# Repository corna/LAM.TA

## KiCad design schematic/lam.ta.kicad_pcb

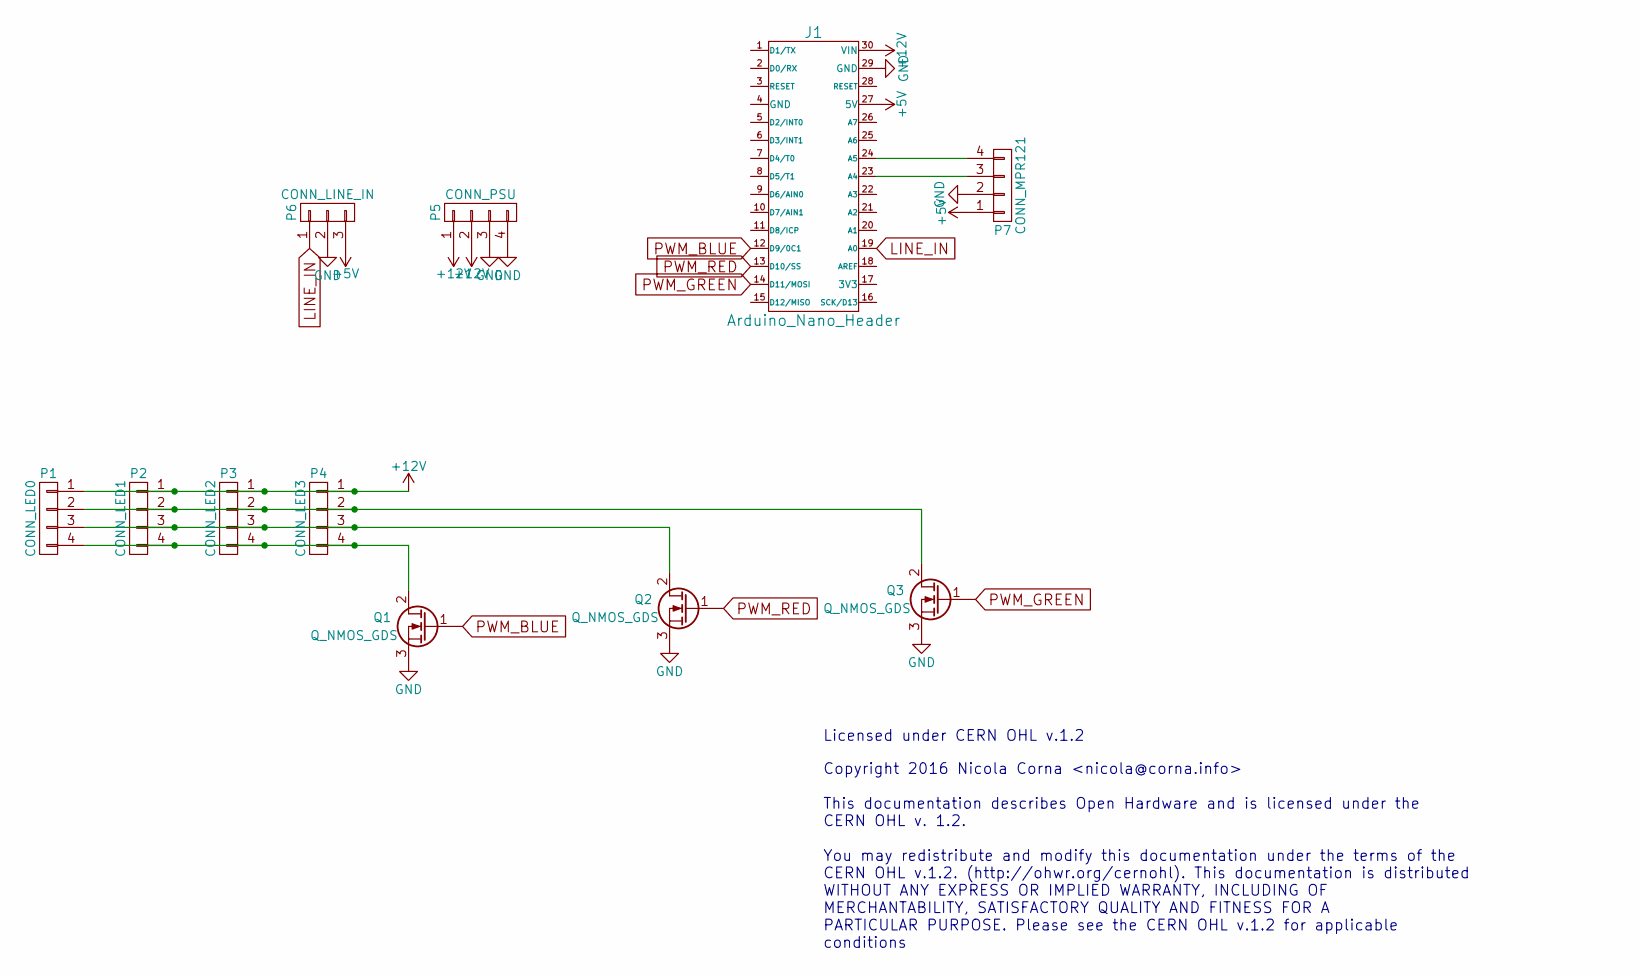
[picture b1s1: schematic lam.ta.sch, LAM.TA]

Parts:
J1: Arduino_Nano_Header; arduino_nano_header
P1: CONN_LED0; Pin_Header_Straight_1x04
P2: CONN_LED1; Pin_Header_Straight_1x04
P3: CONN_LED2; Pin_Header_Straight_1x04
P4: CONN_LED3; Pin_Header_Straight_1x04
P5: CONN_PSU; Pin_Header_Straight_1x04
P6: CONN_LINE_IN; Pin_Header_Straight_1x03
P7: CONN_MPR121; Pin_Header_Straight_1x04
Q1, Q2, Q3: Q_NMOS_GDS; SOT-404

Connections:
+5V: J1.27 (5V), P6.3, P7.1
+12V: J1.30 (VIN), P1.1, P2.1, P3.1, P4.1, P5.1, P5.2
GND: J1.29 (GND), P5.3, P5.4, P6.2, P7.2, Q1.3 (S), Q2.3 (S), Q3.3 (S)
LINE_IN: J1.19 (A0), P6.1
unnamed: J1.23 (A4), P7.3
unnamed: J1.24 (A5), P7.4
unnamed: P1.2, P2.2, P3.2, P4.2, Q3.2 (D)
unnamed: P1.3, P2.3, P3.3, P4.3, Q2.2 (D)
unnamed: P1.4, P2.4, P3.4, P4.4, Q1.2 (D)
PWM_BLUE: J1.12 (D9/0C1), Q1.1 (G)
PWM_GREEN: J1.14 (D11/MOSI), Q3.1 (G)
PWM_RED: J1.13 (D10/SS), Q2.1 (G)

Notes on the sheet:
Licensed under CERN OHL v.1.2
Copyright 2016 Nicola Corna <nicola@corna.info> This documentation describes Open Hardware and is licensed under the CERN OHL v. 1.2. You may redistribute and modify this documentation under the terms of the CERN OHL v.1.2. (http://ohwr.org/cernohl). This documentation is distributed WITHOUT ANY EX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

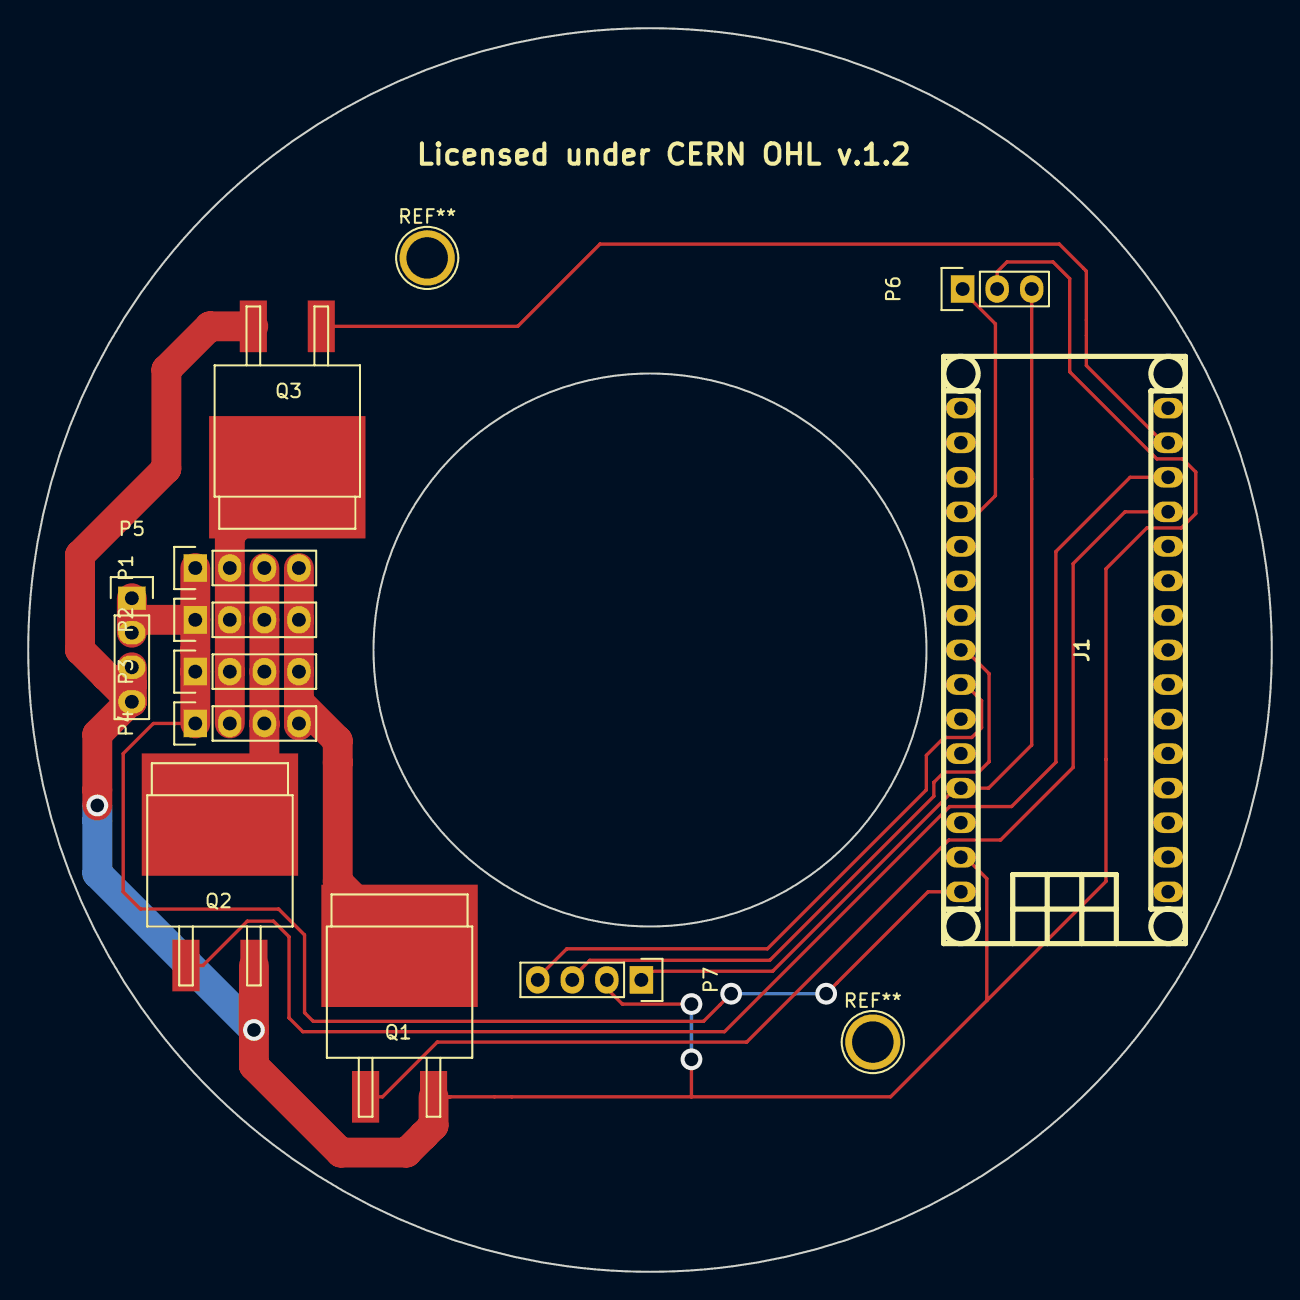
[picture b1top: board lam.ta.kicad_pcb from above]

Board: 2 copper layers, 91.4 x 91.4 mm, 11 parts (0 on the bottom side), 12 nets.

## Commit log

2016-03-15 Update schematic license, replace AT42QT101X with MPR121
2016-03-15 Add RGBFader as submodule
2016-03-15 Add a note about arduino-fsm's timing bug
2016-03-20 Remove old interrupt lines
2016-03-27 Update RGBFader submodule
2016-04-14 Increase noise rejection on MPR121
2016-04-14 Fix double-click bug when powered off
